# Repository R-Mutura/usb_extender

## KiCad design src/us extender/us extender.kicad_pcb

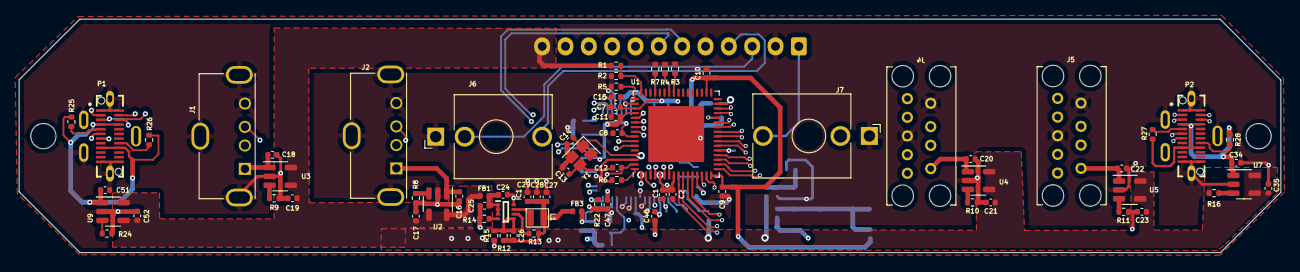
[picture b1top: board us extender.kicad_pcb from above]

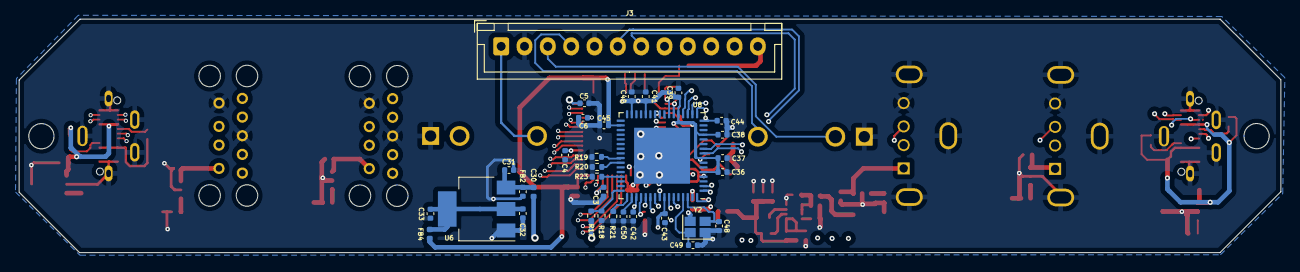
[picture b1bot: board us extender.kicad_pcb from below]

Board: 4 copper layers, 135.2 x 25.0 mm, 106 parts (33 on the bottom side), 89 nets.

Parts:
C1, C2, C3, C4, C5, C6, C7, C8, C9, C10, C11, C12, C15, C31, C33, C36, C37, C38, C39, C40, C41, C42, C43, C44, C45, C46, C47, C50: 100nF; C_0402_1005Metric
C13, C14, C48, C49: 22pF; C_0402_1005Metric
C16, C17, C18, C19, C20, C21, C22, C23, C24, C25, C27, C28, C29, C30, C32, C34, C35, C51, C52: 10uF; C_0402_1005Metric
C26: 10pF; C_0402_1005Metric
FB1, FB2, FB3, FB4: FerriteBead; L_0402_1005Metric
IC1: TPS628501DRLR; SOTFL50P160X60-8N
J1, J2: USB_A; USB_A_Molex_105057_Vertical
J3: Conn_01x12_Male; JST_XH_B12B-XH-A_1x12_P2.50mm_Vertical
J4, J5: GSB412137CHR; AMPHENOL_GSB412137CHR
J6, J7: AudioJack3; Jack_3.5mm_QingPu_WQP-PJ398SM_Vertical_CircularHoles
L1: 330nH; SPH201610HR33MT
P1, P2: USB_C_Plug; GCT_USB4151-GF-C_REVA
R1, R2, R17, R18: 90.9K; R_0402_1005Metric
R3, R4, R7, R19, R20, R23: 1K; R_0402_1005Metric
R5, R13, R15, R21: 100K; R_0402_1005Metric
R6, R22: 9.53K; R_0402_1005Metric
R8, R9, R10, R11, R16, R24: 13.7K; R_0402_1005Metric
R12: 82.5K; R_0402_1005Metric
R14: 8.06K; R_0402_1005Metric
R25, R26, R27, R28: 5.1K; R_0402_1005Metric
U1, U8: TUSB8042AIRGCT; QFN-64-1EP_9x9mm_P0.5mm_EP6x6mm
U2, U3, U4, U5, U7, U9: SY6280AAAC; SOT-23-5
U6: AMS1117-3.3; SOT-223-3_TabPin2
Y1, Y2: 24MHz; Crystal_SMD_EuroQuartz_X22-4Pin_2.5x2.0mm

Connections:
/1.1V 1A/PG: IC1.6 (PG), R13.2
/1.1V 1A/P_IN: C24.1, C25.1, FB1.2, IC1.1 (VIN), IC1.2 (EN), IC1.3 (MODE/SYNC)
/1.1V 1A/P_OUT: C26.1, C27.1, C28.1, C29.1, FB3.1, L1.2, R12.1, R13.1
/3V3 ams1117 1A/P_IN: C30.1, C31.1, FB2.2, U6.3 (VI)
/3V3 ams1117 1A/P_OUT: C32.1, C33.1, FB4.1, U6.2 (VO)
/+1V1_PWR: C1.1, C2.1, C3.1, C4.1, C5.1, C6.1, C7.1, C8.1, C36.1, C37.1, C38.1, C39.1, C40.1, C41.1, C42.1, C43.1, FB3.2, U1.5 (VDD_1), U1.8 (VDD_2), U1.13 (VDD_3), U1.21 (VDD_4), U1.28 (VDD_5), U1.31 (VDD_6), U1.51 (VDD_7), U1.57 (VDD_8), U8.5 (VDD_1), U8.8 (VDD_2), U8.13 (VDD_3), U8.21 (VDD_4), U8.28 (VDD_5), U8.31 (VDD_6), U8.51 (VDD_7), U8.57 (VDD_8)
/+3V3_PWR: C9.1, C10.1, C11.1, C12.1, C44.1, C45.1, C46.1, C47.1, FB4.2, U1.16 (VDD33_1), U1.34 (VDD33_2), U1.52 (VDD33_3), U1.63 (VDD33_4), U8.16 (VDD33_1), U8.34 (VDD33_2), U8.52 (VDD33_3), U8.63 (VDD33_4)
/MIC_IN: J3.1, J7.T
/OVER CURRENT_OVER VOLTAGE PROTECTION1/P_OUT: C18.1, J1.1 (VBUS), U3.1 (VOUT)
/OVER CURRENT_OVER VOLTAGE PROTECTION2/P_OUT: C20.1, J4.1 (VBUS), U4.1 (VOUT)
/OVER CURRENT_OVER VOLTAGE PROTECTION3/P_OUT: C22.1, J5.1 (VBUS), U5.1 (VOUT)
/OVER CURRENT_OVER VOLTAGE PROTECTION4/P_OUT: C34.1, P2.A4 (VBUS), P2.A9 (VBUS), P2.B4 (VBUS), P2.B9 (VBUS), R27.1, R28.1, U7.1 (VOUT)
/OVER CURRENT_OVER VOLTAGE PROTECTION5/P_OUT: C51.1, P1.A4 (VBUS), P1.A9 (VBUS), P1.B4 (VBUS), P1.B9 (VBUS), R25.1, R26.1, U9.1 (VOUT)
/OVER CURRENT_OVER VOLTAGE PROTECTION/P_OUT: C16.1, J2.1 (VBUS), U2.1 (VOUT)
/UP_USB_D+: J3.11, U1.53 (USB_DP_UP)
/UP_USB_D-: J3.10, U1.54 (USB_DM_UP)
/UP_USB_SSRX+: J3.7, U1.58 (USB_SSRXP_UP)
/UP_USB_SSRX-: J3.6, U1.59 (USB_SSRXM_UP)
/UP_USB_SSTX+: J3.9, U1.55 (USB_SSTXP_UP)
/UP_USB_SSTX-: J3.8, U1.56 (USB_SSTXM_UP)
/USB HUB_BRIDGE IC1/USB_DN3_P+: P1.A6 (D+), U8.17 (USB_DP_DN3)
/USB HUB_BRIDGE IC1/USB_DN3_P-: P1.A7 (D-), U8.18 (USB_DM_DN3)
/USB HUB_BRIDGE IC1/USB_DN3_SSRX+: P1.B11 (RX1+), U8.22 (USB_SSRXP_DN3)
/USB HUB_BRIDGE IC1/USB_DN3_SSRX-: P1.B10 (RX1-), U8.23 (USB_SSRXM_DN3)
/USB HUB_BRIDGE IC1/USB_DN3_SSTX+: P1.A2 (TX1+), U8.19 (USB_SSTXP_DN3)
/USB HUB_BRIDGE IC1/USB_DN3_SSTX-: P1.A3 (TX1-), U8.20 (USB_SSTXM_DN3)
/USB HUB_BRIDGE IC/USB_DN1_P+: U1.1 (USB_DP_DN1), U8.53 (USB_DP_UP)
/USB HUB_BRIDGE IC/USB_DN1_P-: U1.2 (USB_DM_DN1), U8.54 (USB_DM_UP)
/USB HUB_BRIDGE IC/USB_DN1_SSRX+: U1.6 (USB_SSRXP_DN1), U8.58 (USB_SSRXP_UP)
/USB HUB_BRIDGE IC/USB_DN1_SSRX-: U1.7 (USB_SSRXM_DN1), U8.59 (USB_SSRXM_UP)
/USB HUB_BRIDGE IC/USB_DN1_SSTX+: U1.3 (USB_SSTXP_DN1), U8.56 (USB_SSTXM_UP)
/USB HUB_BRIDGE IC/USB_DN1_SSTX-: U1.4 (USB_SSTXM_DN1), U8.55 (USB_SSTXP_UP)
/USB HUB_BRIDGE IC/USB_DN2_P+: P2.A6 (D+), U1.9 (USB_DP_DN2)
/USB HUB_BRIDGE IC/USB_DN2_P-: P2.A7 (D-), U1.10 (USB_DM_DN2)
/USB HUB_BRIDGE IC/USB_DN2_SSRX+: P2.B11 (RX1+), U1.14 (USB_SSRXP_DN2)
/USB HUB_BRIDGE IC/USB_DN2_SSRX-: P2.B10 (RX1-), U1.15 (USB_SSRXM_DN2)
/USB HUB_BRIDGE IC/USB_DN2_SSTX+: P2.A2 (TX1+), U1.11 (USB_SSTXP_DN2)
/USB HUB_BRIDGE IC/USB_DN2_SSTX-: P2.A3 (TX1-), U1.12 (USB_SSTXM_DN2)
/USB_DN1_P+: J1.3 (D+), U8.1 (USB_DP_DN1)
/USB_DN1_P-: J1.2 (D-), U8.2 (USB_DM_DN1)
/USB_DN2_P+: J2.3 (D+), U8.9 (USB_DP_DN2)
/USB_DN2_P-: J2.2 (D-), U8.10 (USB_DM_DN2)
/USB_DN3_P+: J4.2 (D-), U1.18 (USB_DM_DN3)
/USB_DN3_P-: J4.3 (D+), U1.17 (USB_DP_DN3)
/USB_DN3_SSRX+: J4.6 (SSRX+), U1.22 (USB_SSRXP_DN3)
/USB_DN3_SSRX-: J4.5 (SSRX-), U1.23 (USB_SSRXM_DN3)
/USB_DN3_SSTX+: J4.9 (SSTX+), U1.19 (USB_SSTXP_DN3)
/USB_DN3_SSTX-: J4.8 (SSTX-), U1.20 (USB_SSTXM_DN3)
/USB_DN4_P+: J5.3 (D+), U1.24 (USB_DP_DN4)
/USB_DN4_P-: J5.2 (D-), U1.25 (USB_DM_DN4)
/USB_DN4_SSRX+: J5.6 (SSRX+), U1.29 (USB_SSRXP_DN4)
/USB_DN4_SSRX-: J5.5 (SSRX-), U1.30 (USB_SSRXM_DN4)
/USB_DN4_SSTX+: J5.9 (SSTX+), U1.26 (USB_SSTXP_DN4)
/USB_DN4_SSTX-: J5.8 (SSTX-), U1.27 (USB_SSTXM_DN4)
/audio_MONO: J3.4, J6.T
/audio_RIGHT: J3.3, J6.R
GND: C1.2, C2.2, C3.2, C4.2, C5.2, C6.2, C7.2, C8.2, C9.2, C10.2, C11.2, C12.2, C13.1, C14.1, C15.2, C16.2, C17.2, C18.2, C19.2, C20.2, C21.2, C22.2, C23.2, C24.2, C25.2, C27.2, C28.2, C29.2, C30.2, C31.2, C32.2, C33.2, C34.2, C35.2, C36.2, C37.2, C38.2, C39.2, C40.2, C41.2, C42.2, C43.2, C44.2, C45.2, C46.2, C47.2, C48.1, C49.1, C50.2, C51.2, C52.2, IC1.8 (GND), J1.4 (GND), J1.5 (Shield), J2.4 (GND), J2.5 (Shield), J3.2, J3.5, J4.4 (GND), J4.7 (GND_DRAIN), J5.4 (GND), J5.7 (GND_DRAIN), J6.S, J7.S, P1.A1 (GND), P1.A12 (GND), P1.B1 (GND), P1.B12 (GND), P1.S1 (SHIELD), P2.A1 (GND), P2.A12 (GND), P2.B1 (GND), P2.B12 (GND), P2.S1 (SHIELD), R2.1, R3.1, R4.1, R5.1, R6.1, R7.1, R8.2, R9.2, R10.2, R11.2, R14.2, R15.2, R16.2, R18.1, R19.1, R20.1, R21.1, R22.1, R23.1, R24.2, U1.65 (EP), U2.2 (GND), U3.2 (GND), U4.2 (GND), U5.2 (GND), U6.1 (GND), U7.2 (GND), U8.65 (EP), U9.2 (GND), Y1.2, Y1.4, Y2.2, Y2.4
unnamed: C13.2, U1.62 (XI), Y1.3
unnamed: C14.2, U1.61 (XO), Y1.1
unnamed: C15.1, U1.50 (GRSTZ)
unnamed: C26.2, IC1.5 (FB), R12.2, R15.1
unnamed: C48.2, U8.62 (XI), Y2.3
unnamed: C49.2, U8.61 (XO), Y2.1
unnamed: C50.1, U8.50 (GRSTZ)
unnamed: IC1.4 (COMP/FSET), R14.1
unnamed: IC1.7 (SW), L1.1
unnamed: P1.A5 (CC), R25.2
unnamed: P1.B5 (VCONN), R26.2
unnamed: P2.A5 (CC), R27.2
unnamed: P2.B5 (VCONN), R28.2
unnamed: R1.2, R2.2, U1.48 (USB_VBUS)
unnamed: R3.2, U1.41 (PWRCTL_POL)
unnamed: R4.2, U1.42 (GANGED/SMBA2/HS_UP)
unnamed: R5.2, U1.49 (TEST)
unnamed: R6.2, U1.64 (USB_R1)
unnamed: R7.2, U1.45 (AUTOENZ/HS_SUSPEND)
unnamed: R8.1, U2.3 (OCB)
unnamed: R9.1, U3.3 (OCB)
unnamed: R10.1, U4.3 (OCB)
unnamed: R11.1, U5.3 (OCB)
unnamed: R16.1, U7.3 (OCB)
unnamed: R17.2, R18.2, U8.48 (USB_VBUS)
unnamed: R19.2, U8.41 (PWRCTL_POL)
unnamed: R20.2, U8.42 (GANGED/SMBA2/HS_UP)
unnamed: R21.2, U8.49 (TEST)
unnamed: R22.2, U8.64 (USB_R1)
unnamed: R23.2, U8.45 (AUTOENZ/HS_SUSPEND)
unnamed: R24.1, U9.3 (OCB)
VBUS: C17.1, C19.1, C21.1, C23.1, C35.1, C52.1, FB1.1, FB2.1, J3.12, R1.1, R17.1, U2.4 (EN), U2.5 (1N), U3.4 (EN), U3.5 (1N), U4.4 (EN), U4.5 (1N), U5.4 (EN), U5.5 (1N), U7.4 (EN), U7.5 (1N), U9.4 (EN), U9.5 (1N)

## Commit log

2022-04-19 finished usb extender
